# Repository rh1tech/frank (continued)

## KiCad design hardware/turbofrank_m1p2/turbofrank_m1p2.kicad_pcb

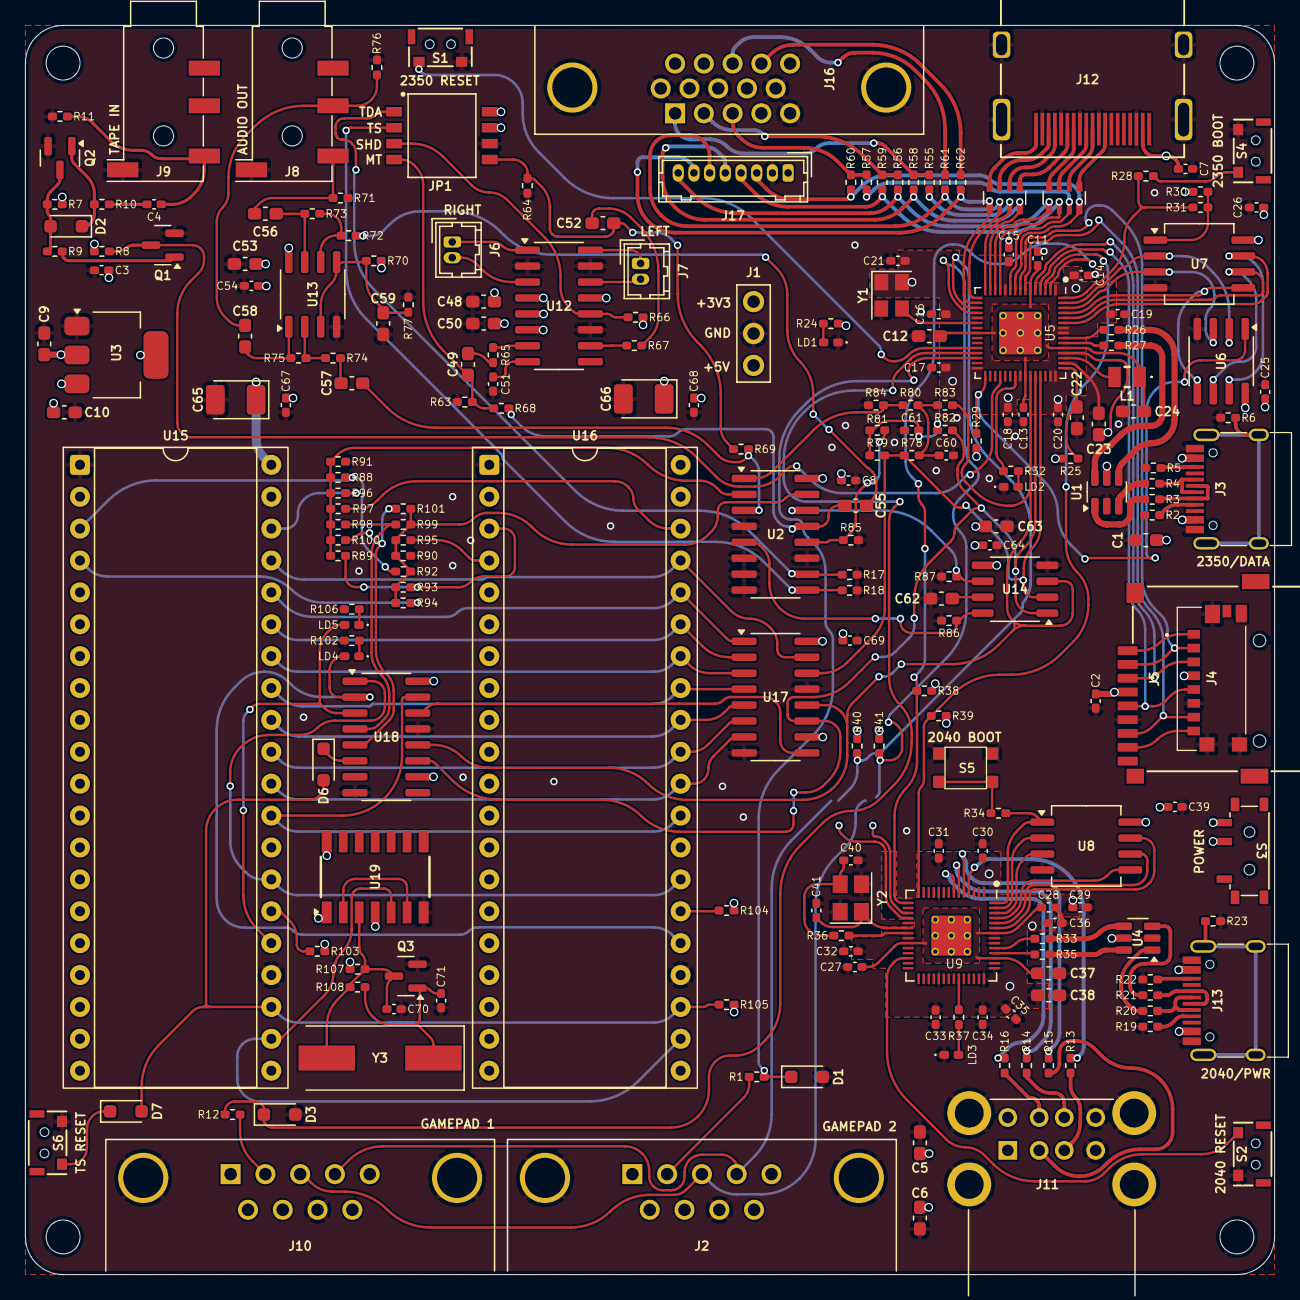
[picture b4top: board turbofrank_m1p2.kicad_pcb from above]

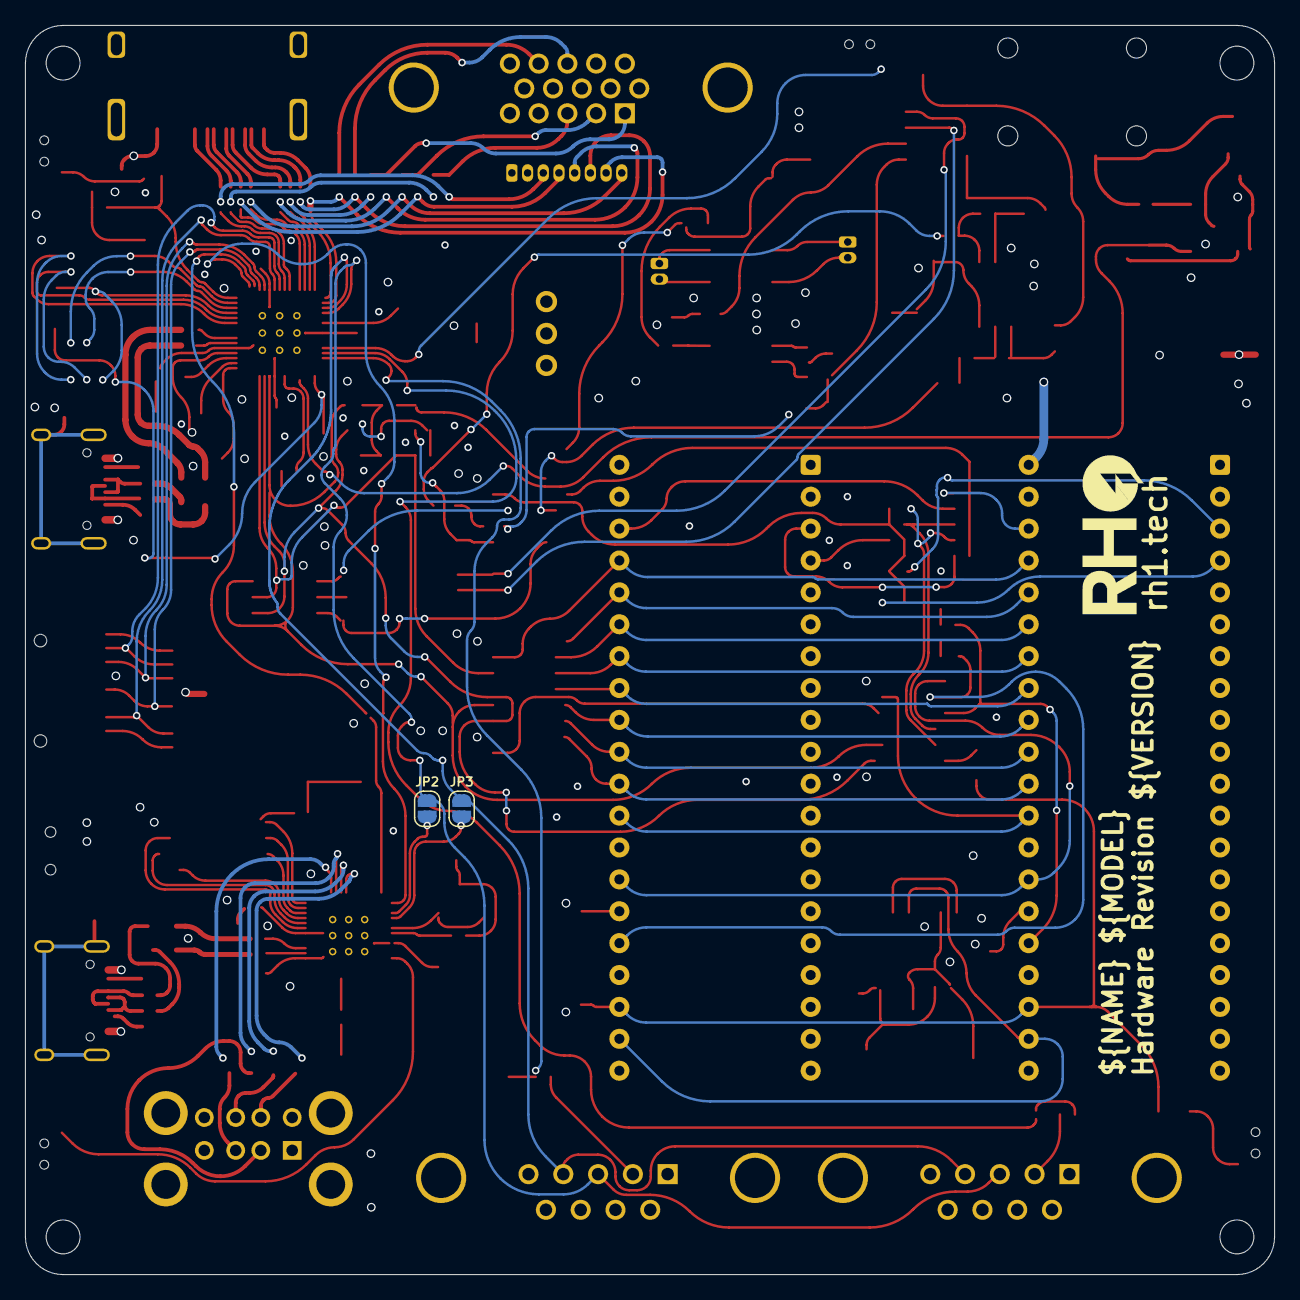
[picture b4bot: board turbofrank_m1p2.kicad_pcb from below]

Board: 4 copper layers, 99.5 x 99.5 mm, 224 parts (2 on the bottom side), 177 nets.

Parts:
C1, C5, C6, C9, C10, C53, C55, C56, C57, C58, C59, C62, C63: 10u; Capacitor (0603)
C2, C3, C4, C7, C8, C11, C13, C14, C15, C16, C17, C18, C19, C20, C21, C25, C26, C27, C28, C29, C30, C31, C32, C33, C34, C35, C36, C39, C51, C54, C64, C67, C68, C69: 100n; Capacitor (0402)
C12, C22, C23, C24: 4.7u; Capacitor (0603)
C37, C38, C48, C49, C52: 1u; Capacitor (0603)
C40, C41: 15p; Capacitor (0402)
C50: 47u; Capacitor (0603)
C60, C61: 47n; Capacitor (0402)
C65, C66: 100u; Capacitor (3528, tantalum, polar)
C70, C71: 22p; Capacitor (0402)
D1, D3: 3V3; Diode (SOD-323)
D2, D6, D7: 1N4148; Diode (SOD-323)
H1, H2, H3, H4: MountingHole; Mounting Hole (2.7mm)
J1: PWR; Pin Header (1x03)
J2, J10: D-SUB 9 Male; D-SUB (9 pin, male, top mount)
J3, J13: USB4215-03-A; USB Type C
J4: 0475710001; MicroSD (SMD, short)
J5: 104031-0811; MicroSD (SMD, long)
J6: PAM L; Connector Female 1.25 JST 2P
J7: PAM R; Connector Female 1.25 JST 2P
J8, J9: PJ-320D; Jack (3.5mm, PJ-320D)
J11: SS-52100-004; USB Type A (stacked)
J12: DC3RX19JA2; HDMI (female)
J16: D-SUB 15 Female; D-SUB (15 pin, female)
J17: Pin Header 1x08; Connector Female 1.25 JST 8P
JP1: Main Jumpers; SW_DS05-127-2-04BK-SMT-TR
JP2: Mouse (DATA); Jumper (solder)
JP3: Mouse (CLK); Jumper (solder)
L1: 3.3u; Inductor (0806)
LD1: Power; LED (0402)
LD2, LD3: Blue; LED (0402)
LD4, LD5: Orange; LED (0402)
Q1, Q2, Q3: BC850; SOT-23
R1, R8, R12, R24, R28, R32, R34, R36, R37, R58, R59, R60, R82, R83, R102, R103, R104, R106, R107: 1K; Resistor (0402)
R2, R5, R19, R22: 5.1K; Resistor (0402)
R3, R4, R13, R14, R15, R16, R20, R21: 22R; Resistor (0402)
R6, R23: 1M; Resistor (0402)
R7, R9, R10, R17, R18, R29, R30, R38, R39, R40, R41, R65, R66, R67, R68, R69, R70, R72, R74, R77, R80, R81, R98, R99, R100, R101, R105: 10K; Resistor (0402)
R11, R61, R62: 100R; Resistor (0402)
R25: 33R; Resistor (0402)
R26, R27, R33, R35: 27R; Resistor (0402)
R31: 0R; Resistor (0402)
R55, R56, R57: 330R; Resistor (0402)
R63, R64, R78, R79, R84, R85, R88, R89, R94, R95: 2K; Resistor (0402)
R71, R76: 20K; Resistor (0402)
R73, R75: 47K; Resistor (0402)
R86, R87: 470R; Resistor (0402)
R90, R91: 120R; Resistor (0402)
R92, R93, R96, R97: 4.7K; Resistor (0402)
R108: 100K; Resistor (0402)
RN1, RN2: 270R; Resistor Array (4x0603)
S1: Reset RP2530A; TACT-SIDE-4623
S2: Reset RP2040; TACT-SIDE-4623
S3: MSK12C02; Switch (MSK12C02)
S4: Boot 2350; TACT-SIDE-4623
S5: Boot 2040; Button (SMD, 3x3mm, 1-1)
S6: KLS7-TS3302; TACT-SIDE-4623
U1, U4: USBLC6-2SC6; SOT-23-6
U2: 74HC4052D; SOP-16
U3: NCP1117 3.3; SOT-223
U5: RP2350; QFN 60 (RP2350A)
U6: ESP-PSRAM32; SO-8
U7: W25Q128JVS; SOIC-8
U8: W25Q128JVSIQ; SOIC-8
U9: RP2040; QFN 56
U12: PAM8403D; SOP-16
U13: LM358; SO-8
U14: TDA1387T; SO-8
U15, U16: JFC95101; DIP-40 (Socket)
U17, U18: 74HC595; SOP-16
U19: 74HC74; 74HCT74D
Y1: ASE-12MHz; Crystal (3225, active)
Y2: 12 MHz; Crystal (3225)
Y3: 3.58 MHz; Crystal (HC49-S)

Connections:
+1V1: C11.1, C12.1, C13.1, C24.1, L1.1, U5.6 (DVDD), U5.23 (DVDD), U5.39 (DVDD), U5.50 (VREG_FB)
+3V3: C2.2, C3.1, C9.1, C14.1, C15.1, C16.1, C17.1, C18.1, C19.1, C20.1, C21.1, C23.1, C25.1, C26.1, C29.1, C30.1, C31.1, C32.1, C33.1, C34.1, C35.1, C36.1, C38.1, C39.1, J1.1, J4.P4 (VDD), J5.4 (VDD), R7.1, R8.1, R24.2, R25.1, R29.2, R30.1, R38.2, R39.2, R40.2, R41.2, U3.2 (VO), U5.1 (IOVDD), U5.11 (IOVDD), U5.20 (IOVDD), U5.30 (IOVDD), U5.38 (IOVDD), U5.44 (ADC_AVDD), U5.45 (IOVDD), U5.49 (VREG_VIN), U5.53 (USB_OTP_VDD), U5.54 (QSPI_IOVDD), U6.8 (VCC), U7.8 (VCC), U8.8 (VCC), U9.1 (IOVDD), U9.10 (IOVDD), U9.22 (IOVDD), U9.33 (IOVDD), U9.42 (IOVDD), U9.43 (ADC_AVDD), U9.44 (VREG_IN), U9.48 (USB_VDD), U9.49 (IOVDD), Y1.1 (EN), Y1.4 (Vdd)
/AMP_IN_L: C55.1, R68.1, U2.13 (1Z)
/AMP_IN_R: C57.1, R69.1, U2.3 (2Z)
/Audio Out/AMP_OUTL: C56.2, J8.T, R71.2
/Audio Out/AMP_OUTR: C58.2, J8.R, R76.2
/Audio Out/AMP_PAM_OUTL_M: J6.2, U12.3 (-OUTL)
/Audio Out/AMP_PAM_OUTL_P: J6.1, U12.1 (+OUT_L)
/Audio Out/AMP_PAM_OUTR_M: J7.2, U12.14 (-OUT_R)
/Audio Out/AMP_PAM_OUTR_P: J7.1, U12.16 (+OUT_R)
/Audio Out/TS/A1: R95.2, U16.4 (B)
/Audio Out/TS/A2: R94.2, U15.4 (B)
/Audio Out/TS/B1: R89.2, R93.2, U16.3 (A)
/Audio Out/TS/B2: R88.2, R92.2, U15.3 (A)
/Audio Out/TS/BEEP: R98.2, R99.2, U18.4 (QE)
/Audio Out/TS/C1: R97.2, U16.38 (C)
/Audio Out/TS/C2: R96.2, U15.38 (C)
/Audio Out/TS/CLK_1.75M: U15.22 (CLOCK), U16.22 (CLOCK), U19.5 (Q)
/Audio Out/TS/DA0: U15.37 (DA0), U16.37 (DA0), U17.15 (QA)
/Audio Out/TS/DA1: U15.36 (DA1), U16.36 (DA1), U17.1 (QB)
/Audio Out/TS/DA2: U15.35 (DA2), U16.35 (DA2), U17.2 (QC)
/Audio Out/TS/DA3: U15.34 (DA3), U16.34 (DA3), U17.3 (QD)
/Audio Out/TS/DA4: U15.33 (DA4), U16.33 (DA4), U17.4 (QE)
/Audio Out/TS/DA5: U15.32 (DA5), U16.32 (DA5), U17.5 (QF)
/Audio Out/TS/DA6: U15.31 (DA6), U16.31 (DA6), U17.6 (QG)
/Audio Out/TS/DA7: U15.30 (DA7), U16.30 (DA7), U17.7 (QH)
/Audio Out/TS/SAVE: R100.2, R101.2, U18.5 (QF)
/Audio Out/TS/YM_BC1: U15.29 (BC1), U16.29 (BC1), U18.15 (QA)
/Audio Out/TS/YM_BDIR: U15.27 (BDIR), U16.27 (BDIR), U18.1 (QB)
/Audio Out/TS/YM_CS1: LD4.2 (A), U16.25 (A8), U18.2 (QC)
/Audio Out/TS/YM_CS2: LD5.2 (A), U15.25 (A8), U18.3 (QD)
/Audio Out/TS/YM_RST: D6.2 (A), D7.2 (A), R105.1, U15.23 (~RESET), U16.23 (~RESET)
/Audio Out/TS/YM_SEL1: R104.2, U16.26 (~SEL)
/Audio Out/TS/YM_SEL2: R103.2, U15.26 (~SEL)
/D+: R26.1, U1.4 (I/O2)
/D-: R27.1, U1.6 (I/O1)
/DAT1: J4.P8 (DAT1), J5.8 (DAT1)
/DAT2: J4.P1 (DAT2), J5.1 (DAT2)
/GPIO0: R38.1, U5.2 (GPIO0), U9.15 (GPIO12)
/GPIO1: R39.1, U5.3 (GPIO1), U9.14 (GPIO11)
/GPIO2: J4.P5 (CLK), J5.5 (CLK), U5.4 (GPIO2)
/GPIO3: J4.P3 (CMD), J5.3 (CMD), U5.5 (GPIO3)
/GPIO4: J4.P7 (DAT0), J5.7 (DAT0), U5.7 (GPIO4)
/GPIO5: J4.P2 (CD/DAT3), J5.2 (DAT3/CD), U5.8 (GPIO5)
/GPIO6: J17.3, R60.1, RN1.4 (R4.1), U5.9 (GPIO6)
/GPIO7: R57.1, RN1.3 (R3.1), U5.10 (GPIO7)
/GPIO8: J17.4, R59.1, RN1.2 (R2.1), U5.12 (GPIO8)
/GPIO9: J17.8, R56.1, RN1.1 (R1.1), U5.13 (GPIO9)
/GPIO10: J17.5, R58.1, RN2.4 (R4.1), U5.14 (GPIO10)
/GPIO11: R55.1, RN2.3 (R3.1), U5.15 (GPIO11)
/GPIO12: J17.6, R61.2, RN2.2 (R2.1), U5.16 (GPIO12)
/GPIO13: J17.7, R62.2, RN2.1 (R1.1), U5.17 (GPIO13)
/GPIO14: J2.4, J10.4, JP3.2 (B), R40.1, U5.18 (GPIO14)
/GPIO15: J2.3, J10.3, JP2.2 (B), R41.1, U5.19 (GPIO15)
/GPIO16: D3.1 (K), R12.1, U5.27 (GPIO16)
/GPIO17: D1.1 (K), R1.1, U5.28 (GPIO17)
/GPIO19: R29.1, U5.31 (GPIO19), U6.1 (~CE)
/GPIO22: Q1.3 (C), R8.2, U5.34 (GPIO22)
/GPIO26: R83.2, U5.40 (GPIO26_ADC0), U14.3 (DATA), U17.12 (RCLK), U18.12 (RCLK)
/GPIO27: R82.2, U5.41 (GPIO27_ADC1), U14.1 (SCLK), U17.11 (SRCLK), U18.11 (SRCLK)
/GPIO28: R78.1, R79.1, U5.42 (GPIO28_ADC2), U14.2 (LRCK), U17.14 (SER)
/J_TDA: JP1.1, R17.2, U2.10 (S0)
/J_TS: JP1.2, R18.2, U2.9 (S1)
/MONO_L: C49.1, JP1.4, R63.1, R68.2
/MONO_R: C52.1, JP1.5, R64.1, R69.2
/MS_CLK: JP3.1 (A), U9.18 (GPIO15)
/MS_DATA: JP2.1 (A), U9.17 (GPIO14)
/PWM_OUT_L: R81.2, R85.1, U2.12 (1Y0)
/PWM_OUT_R: R80.2, R84.1, U2.1 (2Y0)
/RP2_D+: R33.1, U4.4 (I/O2)
/RP2_D-: R35.1, U4.6 (I/O1)
/RP2_GPIO2: R13.1, U9.4 (GPIO2)
/RP2_GPIO3: R15.1, U9.5 (GPIO3)
/RP2_GPIO4: R14.1, U9.6 (GPIO4)
/RP2_GPIO5: R16.1, U9.7 (GPIO5)
/RP2_RUN: S2.1, U9.26 (RUN)
/RP2040/GPIO25: R37.2, U9.37 (GPIO25)
/RP2040/QSPI_SCLK: U8.6 (CLK), U9.52 (QSPI_SCLK)
/RP2040/QSPI_SD0: U8.5 (DI(IO0)), U9.53 (QSPI_SD0)
/RP2040/QSPI_SD1: U8.2 (DO(IO1)), U9.55 (QSPI_SD1)
/RP2040/QSPI_SD2: U8.3 (IO2), U9.54 (QSPI_SD2)
/RP2040/QSPI_SD3: U8.7 (IO3), U9.51 (QSPI_SD3)
/RP2040/QSPI_SS: R34.1, U8.1 (~CS), U9.56 (QSPI_SS)
/RP2040/XIN: C41.1, U9.20 (XIN), Y2.1
/RP2040/XOUT: R36.1, U9.21 (XOUT)
/RP2350A/FLASH_SS: R30.2, R31.2, U7.1 (~CS)
/RP2350A/QSPI_SCLK: U5.56 (QSPI_SCLK), U6.6 (SCLK), U7.6 (CLK)
/RP2350A/QSPI_SD0: U5.57 (QSPI_SD0), U6.5 (SI/SIO), U7.5 (DI(IO0))
/RP2350A/QSPI_SD1: U5.59 (QSPI_SD1), U6.2 (SO/SIO), U7.2 (DO(IO1))
/RP2350A/QSPI_SD2: U5.58 (QSPI_SD2), U6.3 (SIO2), U7.3 (IO2)
/RP2350A/QSPI_SD3: U5.55 (QSPI_SD3), U6.7 (SIO3), U7.7 (IO3)
/RP2350A/QSPI_SS: R28.1, R31.1, U5.60 (QSPI_SS)
/RP2350A/VREG_AVDD: C22.1, R25.2, U5.46 (VREG_AVDD)
/RP2350A/VREG_LX: L1.2, U5.48 (VREG_LX)
/RP2350A/XIN: U5.21 (XIN), Y1.3 (OUT)
/RP2350A/~USB_BOOT: R28.2, S4.2
/RUN: S1.1, U5.26 (RUN)
/SHND: JP1.3, R66.2, U12.12 (SHND)
/TDA_L: R87.2, U2.14 (1Y1), U14.6 (A_LEFT)
/TDA_R: R86.1, U2.5 (2Y1), U14.8 (A_RIGHT)
/TS_L: R90.1, R92.1, R93.1, R94.1, R95.1, R99.1, R101.1, U2.15 (1Y2)
/TS_R: R88.1, R89.1, R91.1, R96.1, R97.1, R98.1, R100.1, U2.2 (2Y2)
GND: C1.2, C2.1, C3.2, C5.2, C6.2, C7.2, C8.1, C9.2, C10.2, C11.2, C12.2, C13.2, C14.2, C15.2, C16.2, C17.2, C18.2, C19.2, C20.2, C21.2, C22.2, C23.2, C24.2, C25.2, C26.2, C27.2, C28.2, C29.2, C30.2, C31.2, C32.2, C33.2, C34.2, C35.2, C36.2, C37.2, C38.2, C39.2, C40.2, C41.2, C48.2, C50.2, C51.2, C53.1, C54.1, C59.1, C60.2, C61.2, C62.2, C63.2, C64.2, C65.2, C66.2, C67.2, C68.2, C69.2, C70.1, C71.1, D1.2 (A), D3.2 (A), J1.2, J2.8, J3.1 (GND), J3.12 (GND), J4.G1 (GND_1), J4.G2 (GND_2), J4.G3 (GND_3), J4.P6 (VSS), J5.6 (VSS), J8.S, J9.S, J10.8, J11.4 (GND1), J11.8 (GND2), J11.9 (Shield), J12.2 (G_D2), J12.5 (G_D1), J12.8 (G_D0), J12.11 (G_CLK), J12.17 (G_DDC/CEC), J12.20 (SHIELD1), J12.21 (SHIELD2), J12.22 (SHIELD3), J12.23 (SHIELD4), J13.1 (GND), J13.12 (GND), J16.0, J16.5, J16.6, J16.7, J16.8, J16.10, J17.2, JP1.6, LD1.1 (K), LD2.1 (K), LD3.1 (K), Q1.2 (E), Q2.2 (E), Q3.2 (E), R2.1, R5.1, R6.2, R11.2, R17.1, R18.1, R19.1, R22.1, R23.2, R63.2, R64.2, R71.1, R76.1, R77.1, R84.2, R85.2, R86.2, R87.1, R90.2, R91.2, R102.1, R106.1, S1.2, S2.2, S4.1, S5.2, S6.2, U1.2 (GND), U2.4 (2Y3), U2.6 (~E), U2.7 (VEE), U2.8 (GND), U2.11 (1Y3), U3.1 (GND), U4.2 (GND), U5.47 (VREG_PGND), U5.61 (GND), U6.4 (VSS), U7.4 (GND), U8.4 (GND), U9.19 (TESTEN), U9.57 (GND), U12.2 (PGND), U12.11 (GND), U12.15 (PGND), U13.4 (V-), U14.4 (AGND), U15.1 (VSS), U15.24 (~A9), U16.1 (VSS), U16.24 (~A9), U17.8 (GND), U17.13 (~OE), U18.8 (GND), U18.13 (~OE), U19.7 (GND), Y1.2 (GND), Y2.2, Y2.4
GPIO25: R32.2, U5.37 (GPIO25)
unnamed: C4.1, J9.T, R11.1
unnamed: C4.2, R10.1
unnamed: C40.1, R36.2, Y2.3
unnamed: C49.2, R65.2
unnamed: C52.2, R67.2
unnamed: C55.2, R72.2
unnamed: C56.1, R73.1, U13.7
unnamed: C57.2, R74.2
unnamed: C58.1, R75.1, U13.1
unnamed: C60.1, R78.2, R80.1, R83.1
unnamed: C61.1, R79.2, R81.1, R82.1
unnamed: D2.2 (A), Q2.3 (C), R7.2, R9.1
unnamed: D2.1 (K), Q2.1 (B), R10.2
unnamed: D6.1 (K), U18.6 (QG)
unnamed: D7.1 (K), S6.1
unnamed: J2.2, R1.2
unnamed: J3.4 (CC1), R2.2
unnamed: J3.10 (CC2), R5.2
unnamed: J3.5 (DN2), J3.7 (DN1), R3.2
unnamed: J3.6 (DP1), J3.8 (DP2), R4.2
unnamed: J3.13 (SHIELD), R6.1
unnamed: J10.2, R12.2
unnamed: J11.3 (D1+), R13.2
unnamed: J11.2 (D1-), R15.2
unnamed: J11.7 (D2+), R14.2
unnamed: J11.6 (D2-), R16.2
unnamed: J12.12 (CLKN), RN1.5 (R4.2)
unnamed: J12.10 (CLKP), RN1.6 (R3.2)
unnamed: J12.9 (D0N), RN1.7 (R2.2)
unnamed: J12.7 (D0P), RN1.8 (R1.2)
unnamed: J12.6 (D1N), RN2.5 (R4.2)
unnamed: J12.4 (D1P), RN2.6 (R3.2)
unnamed: J12.3 (D2N), RN2.7 (R2.2)
unnamed: J12.1 (D2P), RN2.8 (R1.2)
unnamed: J13.4 (CC1), R19.2
unnamed: J13.10 (CC2), R22.2
unnamed: J13.5 (DN2), J13.7 (DN1), R20.2
unnamed: J13.6 (DP1), J13.8 (DP2), R21.2
unnamed: J13.13 (SHIELD), R23.1
unnamed: J16.1, R55.2, R58.2
unnamed: J16.2, R56.2, R59.2
unnamed: J16.3, R57.2, R60.2
unnamed: J16.13, R61.1
unnamed: J16.14, R62.1
unnamed: LD1.2 (A), R24.1
unnamed: LD2.2 (A), R32.1
unnamed: LD3.2 (A), R37.1
unnamed: LD4.1 (K), R102.2
unnamed: LD5.1 (K), R106.2
unnamed: Q1.1 (B), R9.2
unnamed: C71.2, Q3.1 (B), R108.1, Y3.1
unnamed: C70.2, Q3.3 (C), R107.1, R108.2, U19.3 (C), Y3.2
unnamed: R3.1, U1.1 (I/O1)
unnamed: R4.1, U1.3 (I/O2)
unnamed: R20.1, U4.1 (I/O1)
unnamed: R21.1, U4.3 (I/O2)
unnamed: R34.2, S5.1
unnamed: J13.2 (VBUS), J13.11 (VBUS), S3.2 (B)
unnamed: R27.2, U5.51 (USB_DM)
unnamed: R26.2, U5.52 (USB_DP)
unnamed: R35.2, U9.46 (USB_DM)
unnamed: R33.2, U9.47 (USB_DP)
unnamed: C27.1, C28.1, C37.1, U9.23 (DVDD), U9.45 (VREG_VOUT), U9.50 (DVDD)
unnamed: R65.1, U12.7 (INL)
unnamed: R67.1, U12.10 (INR)
unnamed: C51.1, U12.8 (VREF)
unnamed: C59.2, R70.1, R77.2, U13.3 (+), U13.5 (+)
unnamed: R74.1, R75.2, U13.2 (-)
unnamed: R72.1, R73.2, U13.6 (-)
unnamed: C62.1, U14.7 (FLT)
unnamed: U17.9 (QH'), U18.14 (SER)
unnamed: U19.2 (D), U19.6 (~Q)
VBUS: C1.1, C5.1, C6.1, C7.1, C8.2, C10.1, C48.1, C50.1, C53.2, C54.2, C63.1, C64.1, C65.1, C66.1, C67.1, C68.1, C69.1, J1.3, J2.6, J3.2 (VBUS), J3.11 (VBUS), J10.6, J11.1 (VBUS1), J11.5 (VBUS2), J12.18 (+5V), J17.1, JP1.7, JP1.8, R66.1, R70.2, R103.1, R104.1, R105.2, R107.2, S3.3 (A), U1.5 (VBUS), U2.16 (VCC), U3.3 (VI), U4.5 (VBUS), U12.4 (PVDD), U12.5 (MUTE), U12.6 (VDD), U12.13 (PVDD), U13.8 (V+), U14.5 (VA), U15.28 (BC2), U15.40 (VCC), U16.28 (BC2), U16.40 (VCC), U17.10 (~SRCLR), U17.16 (VCC), U18.10 (~SRCLR), U18.16 (VCC), U19.1 (~R), U19.4 (~S), U19.14 (VCC)

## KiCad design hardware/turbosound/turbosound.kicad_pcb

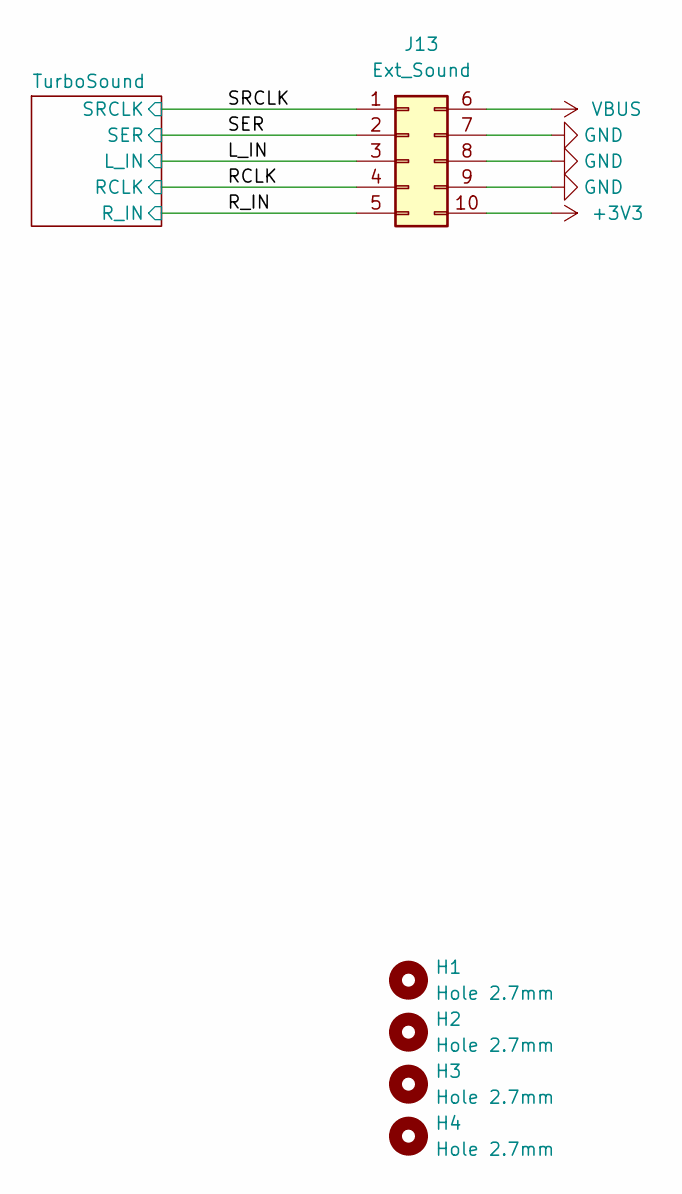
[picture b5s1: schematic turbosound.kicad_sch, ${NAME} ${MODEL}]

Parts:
H1, H2, H3, H4: Hole 2.7mm; MountingHole_2.7mm
J13: Ext_Sound; IDC-Header_2x05_P2.54mm_Vertical

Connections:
+3V3: J13.10
/L_IN: J13.3; also elsewhere on the board
/RCLK: J13.4; also elsewhere on the board
/R_IN: J13.5; also elsewhere on the board
/SER: J13.2; also elsewhere on the board
/SRCLK: J13.1; also elsewhere on the board
GND: J13.7, J13.8, J13.9; also elsewhere on the board
VBUS: J13.6; also elsewhere on the board

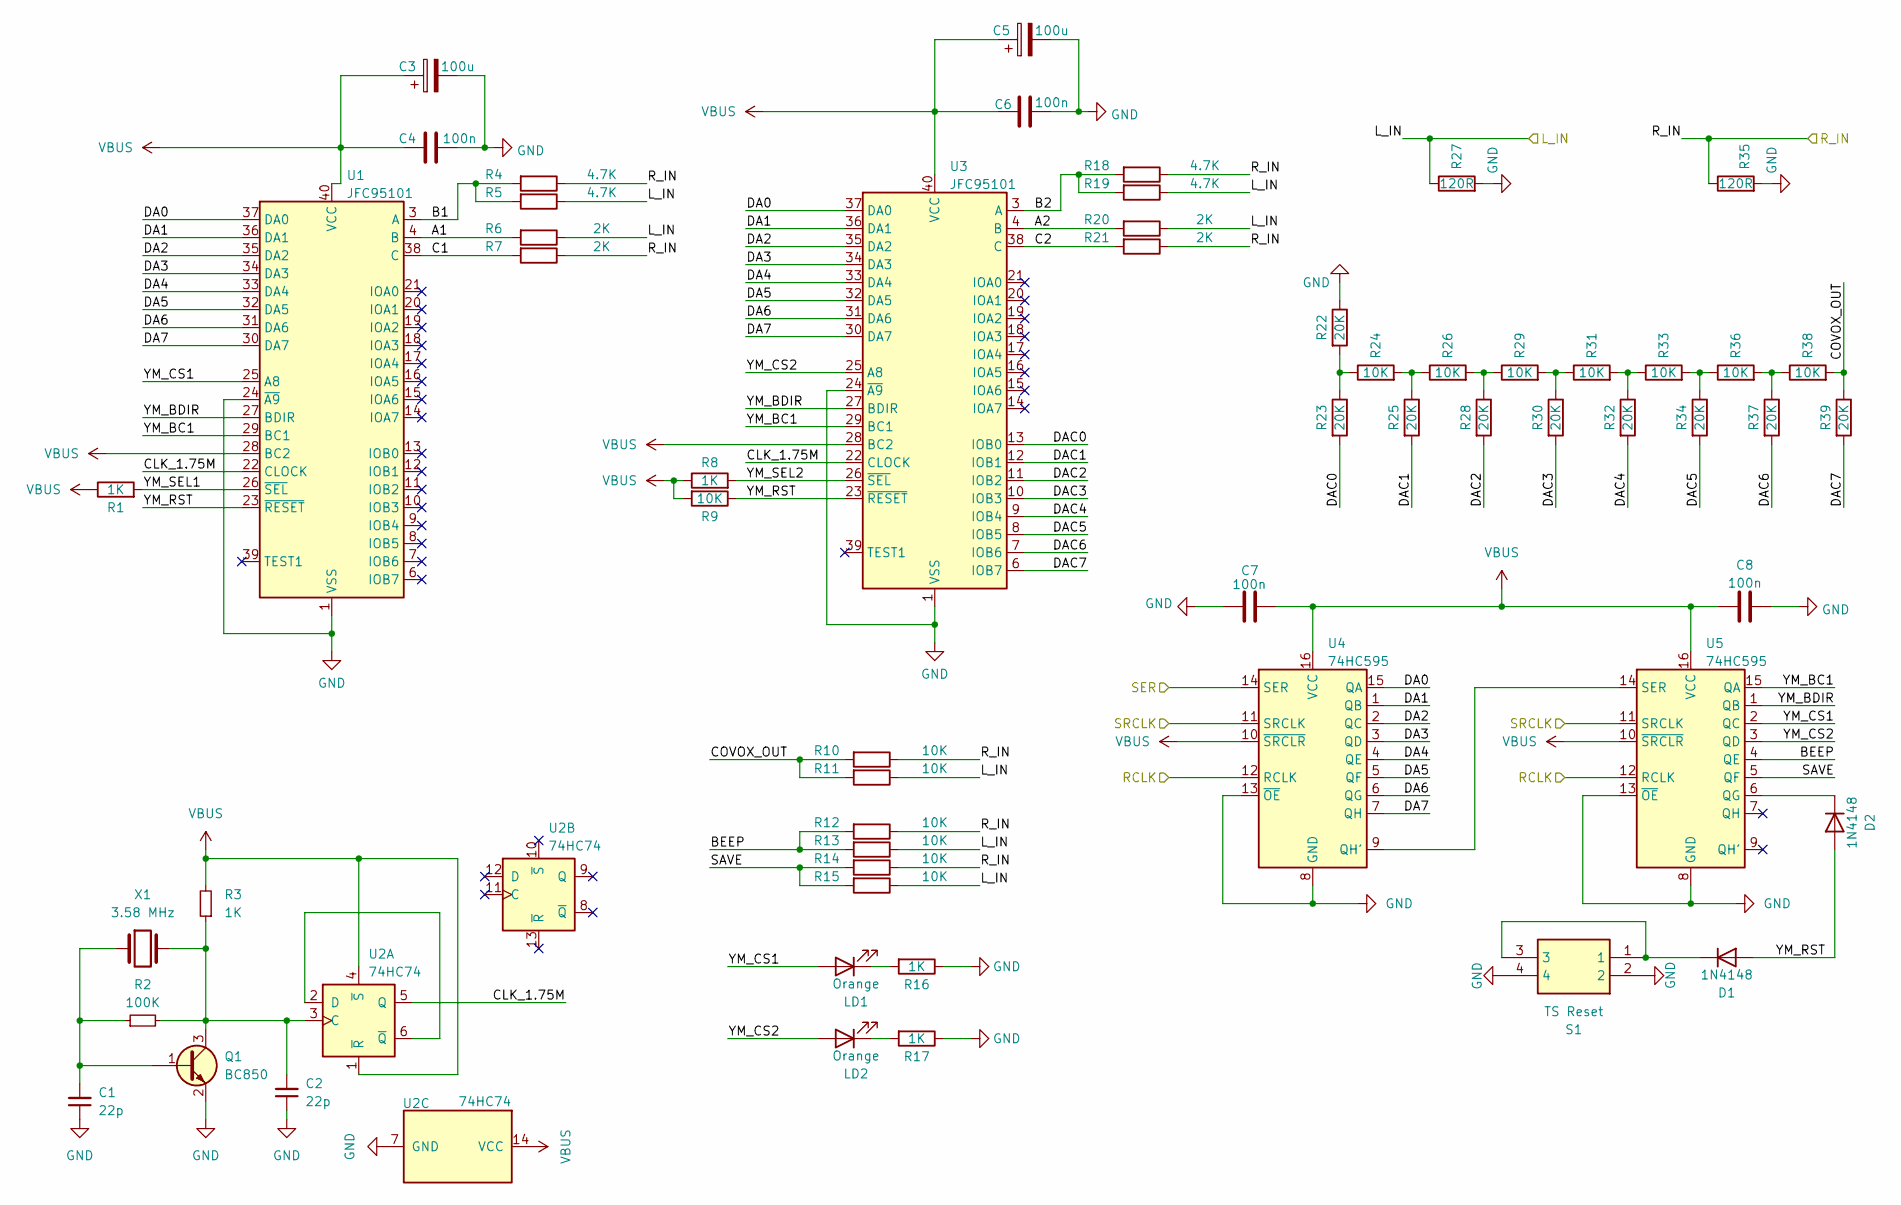
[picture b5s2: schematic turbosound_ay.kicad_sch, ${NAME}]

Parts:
C1, C2: 22p; C_0603_1608Metric
C3, C5: 100u; CP_EIA-3528-12_Kemet-T
C4, C6, C7, C8: 100n; C_0603_1608Metric
D1, D2: 1N4148; D_SOD-323
LD1, LD2: Orange; LED_0805_2012Metric
Q1: BC850; SOT-23
R1, R3, R8, R16, R17: 1K; R_0603_1608Metric
R2: 100K; R_0603_1608Metric
R4, R5, R18, R19: 4.7K; R_0603_1608Metric
R6, R7, R20, R21: 2K; R_0603_1608Metric
R9, R10, R11, R12, R13, R14, R15, R24, R26, R29, R31, R33, R36, R38: 10K; R_0603_1608Metric
R22, R23, R25, R28, R30, R32, R34, R37, R39: 20K; R_0603_1608Metric
R27, R35: 120R; R_0603_1608Metric
S1: TS Reset; KMR_2; Mouser Part Number 611-KMR221G-LFS
U1, U3: JFC95101; DIP-40_W15.24mm_Socket
U2: 74HC74; 74HCT74D
U4, U5: 74HC595; SOP-16_3.9x9.9mm_P1.27mm
X1: 3.58 MHz; Crystal_HC49-S

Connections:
/L_IN: R5.1, R6.1, R11.1, R13.1, R15.1, R19.1, R20.1, R27.1; also elsewhere on the board
/RCLK: U4.12 (RCLK), U5.12 (RCLK); also elsewhere on the board
/R_IN: R4.1, R7.1, R10.1, R12.1, R14.1, R18.1, R21.1, R35.1; also elsewhere on the board
/SER: U4.14 (SER); also elsewhere on the board
/SRCLK: U4.11 (SRCLK), U5.11 (SRCLK); also elsewhere on the board
/TurboSound/A1: R6.2, U1.4 (B)
/TurboSound/A2: R20.2, U3.4 (B)
/TurboSound/B1: R4.2, R5.2, U1.3 (A)
/TurboSound/B2: R18.2, R19.2, U3.3 (A)
/TurboSound/BEEP: R12.2, R13.2, U5.4 (QE)
/TurboSound/C1: R7.2, U1.38 (C)
/TurboSound/C2: R21.2, U3.38 (C)
/TurboSound/CLK_1.75M: U1.22 (CLOCK), U2.5 (Q), U3.22 (CLOCK)
/TurboSound/COVOX_OUT: R10.2, R11.2, R38.2, R39.1
/TurboSound/DA0: U1.37 (DA0), U3.37 (DA0), U4.15 (QA)
/TurboSound/DA1: U1.36 (DA1), U3.36 (DA1), U4.1 (QB)
/TurboSound/DA2: U1.35 (DA2), U3.35 (DA2), U4.2 (QC)
/TurboSound/DA3: U1.34 (DA3), U3.34 (DA3), U4.3 (QD)
/TurboSound/DA4: U1.33 (DA4), U3.33 (DA4), U4.4 (QE)
/TurboSound/DA5: U1.32 (DA5), U3.32 (DA5), U4.5 (QF)
/TurboSound/DA6: U1.31 (DA6), U3.31 (DA6), U4.6 (QG)
/TurboSound/DA7: U1.30 (DA7), U3.30 (DA7), U4.7 (QH)
/TurboSound/DAC0: R23.2, U3.13 (IOB0)
/TurboSound/DAC1: R25.2, U3.12 (IOB1)
/TurboSound/DAC2: R28.2, U3.11 (IOB2)
/TurboSound/DAC3: R30.2, U3.10 (IOB3)
/TurboSound/DAC4: R32.2, U3.9 (IOB4)
/TurboSound/DAC5: R34.2, U3.8 (IOB5)
/TurboSound/DAC6: R37.2, U3.7 (IOB6)
/TurboSound/DAC7: R39.2, U3.6 (IOB7)
/TurboSound/SAVE: R14.2, R15.2, U5.5 (QF)
/TurboSound/YM_BC1: U1.29 (BC1), U3.29 (BC1), U5.15 (QA)
/TurboSound/YM_BDIR: U1.27 (BDIR), U3.27 (BDIR), U5.1 (QB)
/TurboSound/YM_CS1: LD1.2 (A), U1.25 (A8), U5.2 (QC)
/TurboSound/YM_CS2: LD2.2 (A), U3.25 (A8), U5.3 (QD)
/TurboSound/YM_RST: D1.2 (A), D2.2 (A), R9.1, U1.23 (~RESET), U3.23 (~RESET)
/TurboSound/YM_SEL1: R1.2, U1.26 (~SEL)
/TurboSound/YM_SEL2: R8.2, U3.26 (~SEL)
GND: C1.1, C2.1, C3.2, C4.2, C5.2, C6.2, C7.2, C8.2, Q1.2 (E), R16.1, R17.1, R22.1, R27.2, R35.2, S1.2, S1.4, U1.1 (VSS), U1.24 (~A9), U2.7 (GND), U3.1 (VSS), U3.24 (~A9), U4.8 (GND), U4.13 (~OE), U5.8 (GND), U5.13 (~OE); also elsewhere on the board
unnamed: D1.1 (K), S1.1, S1.3
unnamed: D2.1 (K), U5.6 (QG)
unnamed: LD1.1 (K), R16.2
unnamed: LD2.1 (K), R17.2
unnamed: C1.2, Q1.1 (B), R2.1, X1.1
unnamed: C2.2, Q1.3 (C), R2.2, R3.1, U2.3 (C), X1.2
unnamed: R22.2, R23.1, R24.1
unnamed: R24.2, R25.1, R26.1
unnamed: R26.2, R28.1, R29.1
unnamed: R29.2, R30.1, R31.1
unnamed: R31.2, R32.1, R33.1
unnamed: R33.2, R34.1, R36.1
unnamed: R36.2, R37.1, R38.1
unnamed: U2.2 (D), U2.6 (~Q)
unnamed: U4.9 (QH'), U5.14 (SER)
VBUS: C3.1, C4.1, C5.1, C6.1, C7.1, C8.1, R1.1, R3.2, R8.1, R9.2, U1.28 (BC2), U1.40 (VCC), U2.1 (~R), U2.4 (~S), U2.14 (VCC), U3.28 (BC2), U3.40 (VCC), U4.10 (~SRCLR), U4.16 (VCC), U5.10 (~SRCLR), U5.16 (VCC); also elsewhere on the board

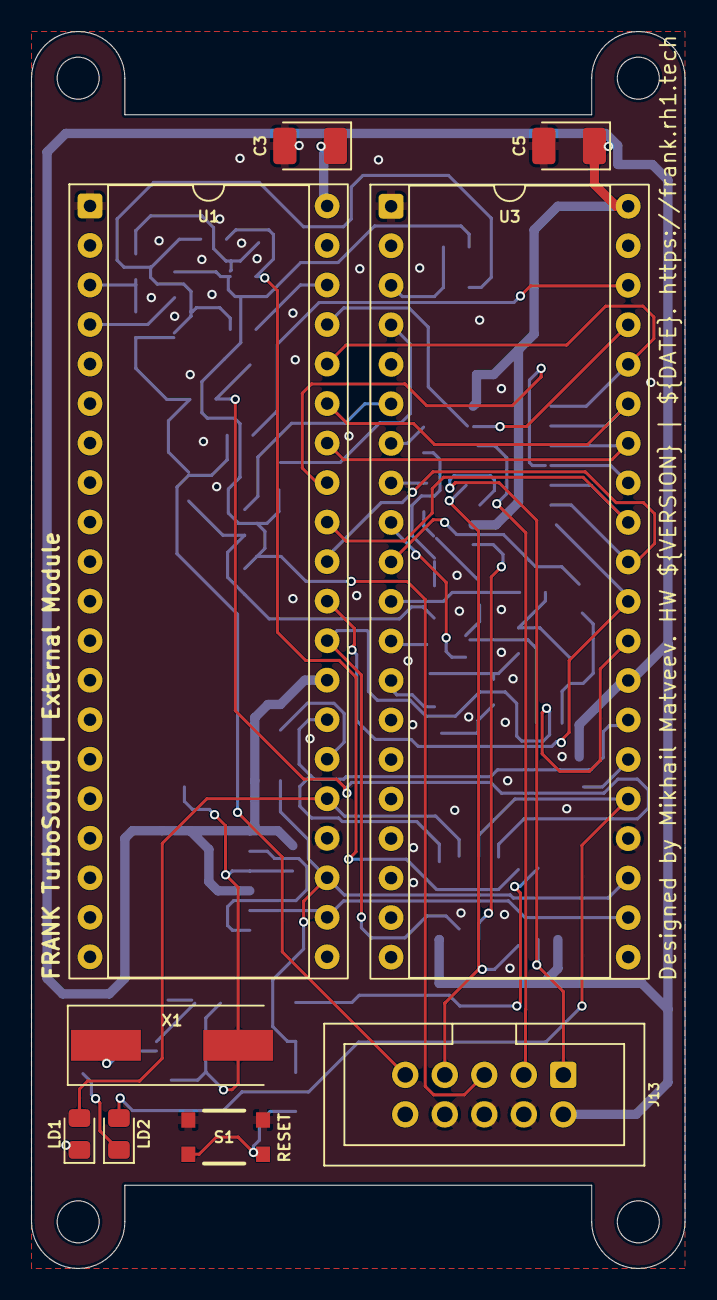
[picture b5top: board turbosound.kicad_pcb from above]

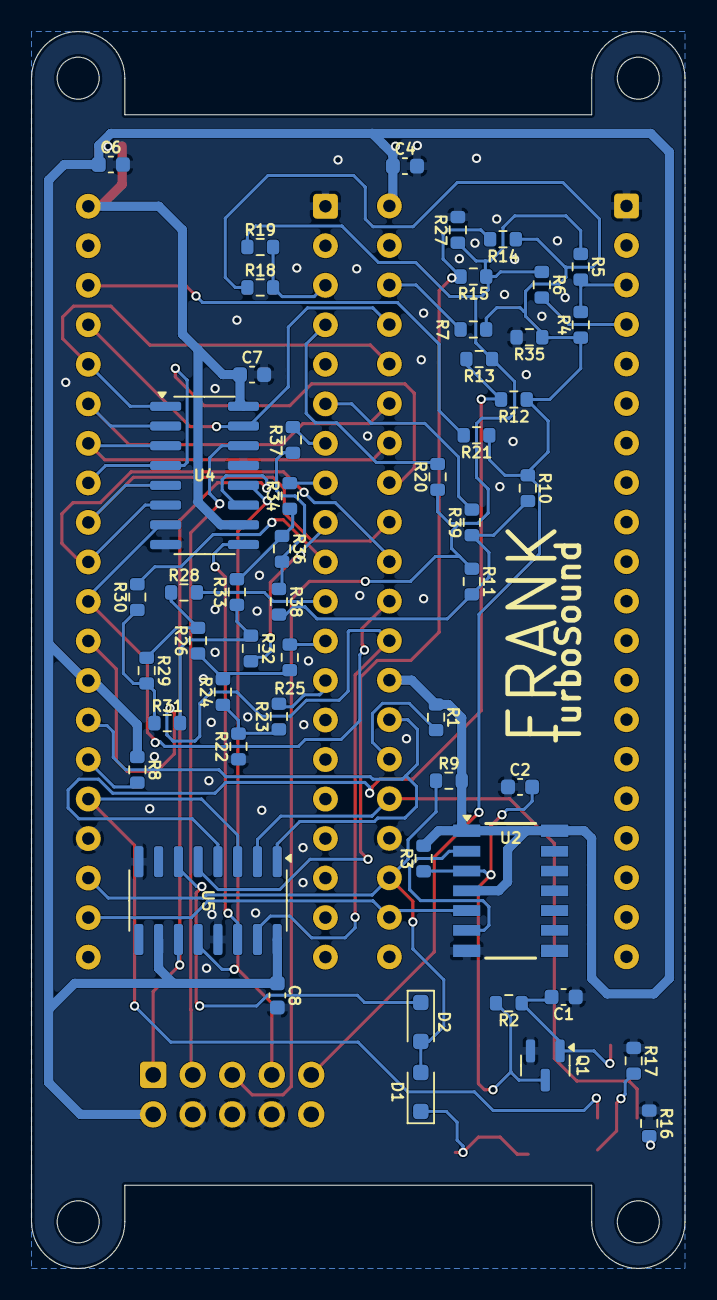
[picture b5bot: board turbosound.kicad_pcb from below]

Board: 2 copper layers, 42.0 x 79.5 mm, 64 parts (51 on the bottom side), 55 nets.

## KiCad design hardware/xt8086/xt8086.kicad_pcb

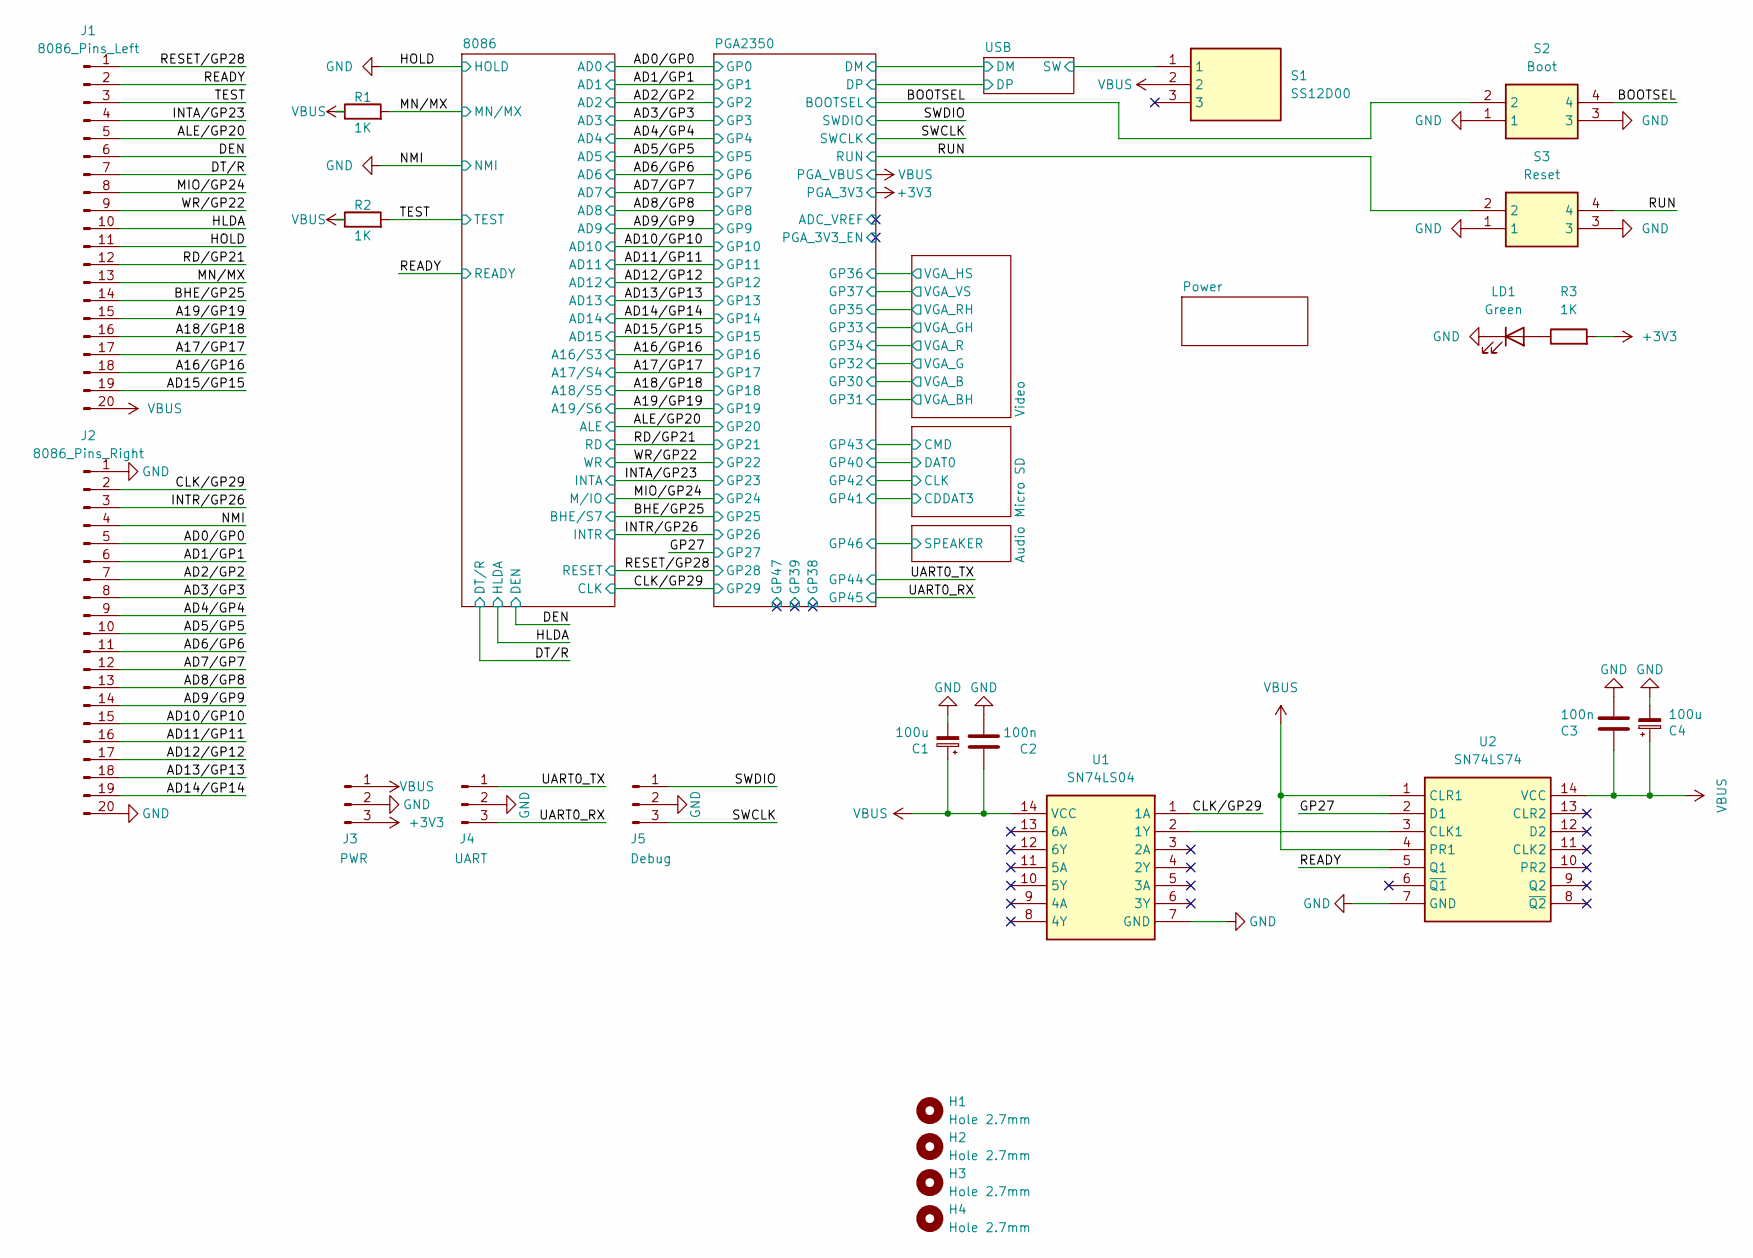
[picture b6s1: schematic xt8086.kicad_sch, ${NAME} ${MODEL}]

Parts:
C1, C4: 100u; CP_Radial_D6.3mm_P2.50mm
C2, C3: 100n; C_0805_2012Metric
H1, H2, H3, H4: Hole 2.7mm; MountingHole_2.7mm
J1: 8086_Pins_Left; PinSocket_1x20_P2.54mm_Vertical
J2: 8086_Pins_Right; PinSocket_1x20_P2.54mm_Vertical
J3: PWR; PinHeader_1x03_P2.54mm_Vertical
J4: UART; JST_SH_1x03_P1.00mm_Vertical
J5: Debug; JST_SH_1x03_P1.00mm_Vertical
LD1: Green; LED_0805_2012Metric_Pad1.15x1.40mm_HandSolder
R1, R2, R3: 1K; R_0805_2012Metric
S1: SS12D00; Switch_Slide_SS12D00; Mouser Part Number 611-SK12D07VG3NS
S2: Boot; Button_SMD_3x4x2mm; Mouser Part Number 611-KMR221G-LFS
S3: Reset; Button_SMD_3x4x2mm; Mouser Part Number 611-KMR221G-LFS
U1: SN74LS04; DIP-14_W7.62mm; Mouser Part Number 595-SN74LS04N
U2: SN74LS74; DIP-14_W7.62mm; Mouser Part Number 595-SN74LS74ANE4

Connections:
+3V3: J3.3, R3.2; also elsewhere on the board
/A16/GP16: J1.18; also elsewhere on the board
/A17/GP17: J1.17; also elsewhere on the board
/A18/GP18: J1.16; also elsewhere on the board
/A19/GP19: J1.15; also elsewhere on the board
/AD0/GP0: J2.5; also elsewhere on the board
/AD1/GP1: J2.6; also elsewhere on the board
/AD2/GP2: J2.7; also elsewhere on the board
/AD3/GP3: J2.8; also elsewhere on the board
/AD4/GP4: J2.9; also elsewhere on the board
/AD5/GP5: J2.10; also elsewhere on the board
/AD6/GP6: J2.11; also elsewhere on the board
/AD7/GP7: J2.12; also elsewhere on the board
/AD8/GP8: J2.13; also elsewhere on the board
/AD9/GP9: J2.14; also elsewhere on the board
/AD10/GP10: J2.15; also elsewhere on the board
/AD11/GP11: J2.16; also elsewhere on the board
/AD12/GP12: J2.17; also elsewhere on the board
/AD13/GP13: J2.18; also elsewhere on the board
/AD14/GP14: J2.19; also elsewhere on the board
/AD15/GP15: J1.19; also elsewhere on the board
/ALE/GP20: J1.5; also elsewhere on the board
/BOOTSEL: S2.2, S2.4; also elsewhere on the board
/CLK/GP29: J2.2, U1.1 (1A); also elsewhere on the board
/DEN: J1.6; also elsewhere on the board
/DT/R: J1.7; also elsewhere on the board
/GP27: U2.2 (D1); also elsewhere on the board
/HLDA: J1.10; also elsewhere on the board
/INTA/GP23: J1.4; also elsewhere on the board
/INTR/GP26: J2.3; also elsewhere on the board
/MIO/GP24: J1.8; also elsewhere on the board
/MN/MX: J1.13, R1.2; also elsewhere on the board
/RD/GP21: J1.12; also elsewhere on the board
/READY: J1.2, U2.5 (Q1); also elsewhere on the board
/RESET/GP28: J1.1; also elsewhere on the board
/RUN: S3.2, S3.4; also elsewhere on the board
/SWCLK: J5.3; also elsewhere on the board
/SWDIO: J5.1; also elsewhere on the board
/TEST: J1.3, R2.2; also elsewhere on the board
/UART0_RX: J4.3; also elsewhere on the board
/UART0_TX: J4.1; also elsewhere on the board
/USB/SW: S1.1; also elsewhere on the board
/WR/GP22: J1.9; also elsewhere on the board
GND: C1.2, C2.2, C3.2, C4.2, J1.11, J2.1, J2.4, J2.20, J3.2, J4.2, J5.2, LD1.1 (K), S2.1, S2.3, S3.1, S3.3, U1.7 (GND), U2.7 (GND); also elsewhere on the board
GP25: J1.14; also elsewhere on the board
unnamed: LD1.2 (A), R3.1
unnamed: U1.2 (1Y), U2.3 (CLK1)
VBUS: C1.1, C2.1, C3.1, C4.1, J1.20, J3.1, R1.1, R2.1, S1.2, U1.14 (VCC), U2.1 (CLR1), U2.4 (PR1), U2.14 (VCC); also elsewhere on the board
